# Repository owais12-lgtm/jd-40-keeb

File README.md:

# jd-40-keeb

# about

This is a keyboard based on the JD40 layout which has smaller keys and generally small form factor. it has a oled screen, encoder and a number pad

# Images

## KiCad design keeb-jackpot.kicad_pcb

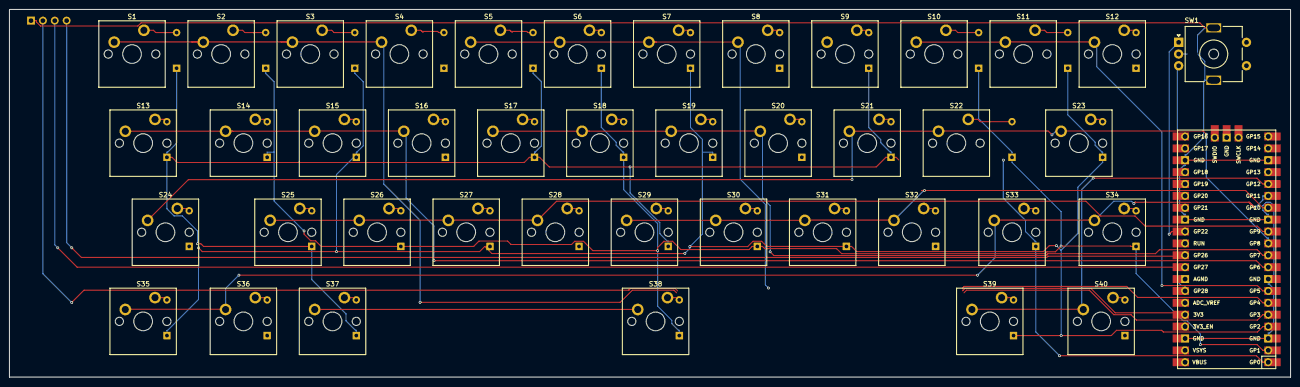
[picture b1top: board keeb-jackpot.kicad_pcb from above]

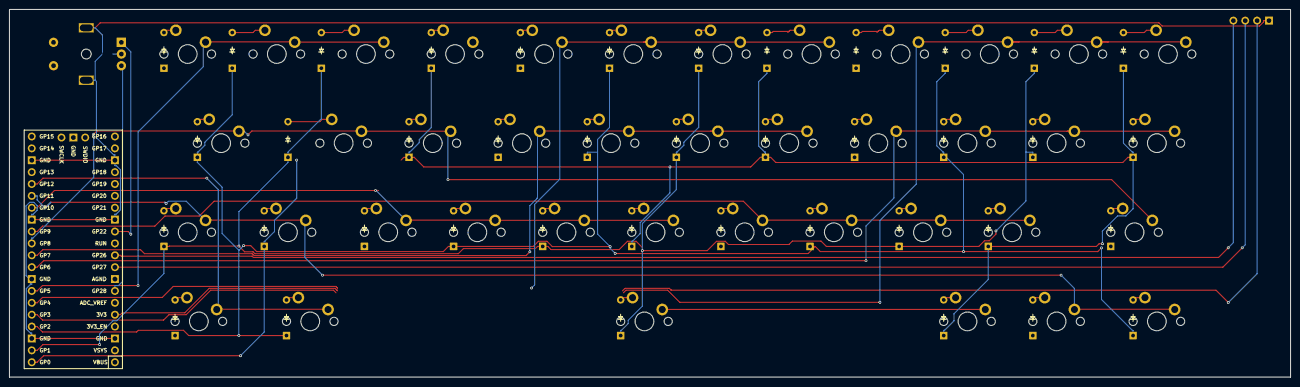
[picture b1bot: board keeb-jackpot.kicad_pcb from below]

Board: 2 copper layers, 273.8 x 78.6 mm, 83 parts (40 on the bottom side), 59 nets.

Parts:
D1, D2, D3, D4, D5, D6, D7, D8, D9, D10, D11, D12, D13, D14, D15, D16, D17, D18, D19, D20, D21, D22, D23, D24, D25, D26, D27, D28, D29, D30, D31, D32, D33, D34, D35, D36, D37, D38, D39, D40: Diode_DO-35
J1: OLED_128x32
S1, S2, S3, S4, S5, S6, S7, S8, S9, S10, S11, S12, S13, S14, S15, S16, S17, S18, S19, S20, S21, S22, S23, S24, S25, S26, S27, S28, S29, S30, S31, S32, S33, S34, S35, S36, S37, S38, S39, S40: MX_PCB_1.00u
SW1: RotaryEncoder_Switch_MP; RotaryEncoder_Alps_EC11E-Switch_Vertical_H20mm_MountingHoles
U1: Raspberry_Pi_Pico

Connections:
COL0: S1.1, S2.1, S3.1, S4.1, U1.5 (GPIO3)
COL1: S5.1, S6.1, S7.1, S8.1, U1.6 (GPIO4)
COL2: S9.1, S10.1, S11.1, S12.1, U1.7 (GPIO5)
COL3: S13.1, S14.1, S15.1, S16.1, U1.9 (GPIO6)
COL4: S17.1, S18.1, S19.1, S20.1, U1.10 (GPIO7)
COL5: S21.1, S22.1, S23.1, S24.1, U1.11 (GPIO8)
COL6: S25.1, S26.1, S27.1, S28.1, U1.12 (GPIO9)
COL7: S29.1, S30.1, S31.1, S32.1, U1.14 (GPIO10)
COL8: S33.1, S34.1, S35.1, S36.1, U1.15 (GPIO11)
COL9: S37.1, S38.1, S39.1, S40.1, U1.16 (GPIO12)
ENC_A: SW1.A, U1.29 (GPIO22)
ENC_B: SW1.B, U1.34 (GPIO28_ADC2)
GND: J1.1 (GND), SW1.C, SW1.MP, U1.3 (GND), U1.8 (GND), U1.13 (GND), U1.18 (GND), U1.23 (GND), U1.28 (GND), U1.38 (GND)
unnamed: D1.2 (A), S1.2
unnamed: D2.2 (A), S2.2
unnamed: D3.2 (A), S3.2
unnamed: D4.2 (A), S4.2
unnamed: D5.2 (A), S5.2
unnamed: D6.2 (A), S6.2
unnamed: D7.2 (A), S7.2
unnamed: D8.2 (A), S8.2
unnamed: D9.2 (A), S9.2
unnamed: D10.2 (A), S10.2
unnamed: D11.2 (A), S11.2
unnamed: D12.2 (A), S12.2
unnamed: D13.2 (A), S13.2
unnamed: D14.2 (A), S14.2
unnamed: D15.2 (A), S15.2
unnamed: D16.2 (A), S16.2
unnamed: D17.2 (A), S17.2
unnamed: D18.2 (A), S18.2
unnamed: D19.2 (A), S19.2
unnamed: D20.2 (A), S20.2
unnamed: D21.2 (A), S21.2
unnamed: D22.2 (A), S22.2
unnamed: D23.2 (A), S23.2
unnamed: D24.2 (A), S24.2
unnamed: D25.2 (A), S25.2
unnamed: D26.2 (A), S26.2
unnamed: D27.2 (A), S27.2
unnamed: D28.2 (A), S28.2
unnamed: D29.2 (A), S29.2
unnamed: D30.2 (A), S30.2
unnamed: D31.2 (A), S31.2
unnamed: D32.2 (A), S32.2
unnamed: D33.2 (A), S33.2
unnamed: D34.2 (A), S34.2
unnamed: D35.2 (A), S35.2
unnamed: D36.2 (A), S36.2
unnamed: D37.2 (A), S37.2
unnamed: D38.2 (A), S38.2
unnamed: D39.2 (A), S39.2
unnamed: D40.2 (A), S40.2
ROW0: D1.1 (K), D5.1 (K), D9.1 (K), D13.1 (K), D17.1 (K), D21.1 (K), D25.1 (K), D29.1 (K), D33.1 (K), D37.1 (K), U1.1 (GPIO0)
ROW1: D2.1 (K), D6.1 (K), D10.1 (K), D14.1 (K), D18.1 (K), D22.1 (K), D26.1 (K), D30.1 (K), D34.1 (K), D38.1 (K), U1.2 (GPIO1)
ROW2: D3.1 (K), D7.1 (K), D11.1 (K), D15.1 (K), D19.1 (K), D23.1 (K), D27.1 (K), D31.1 (K), D35.1 (K), D39.1 (K), U1.4 (GPIO2)
SCL: J1.3 (SCL), U1.32 (GPIO27_ADC1)
SDA: J1.4 (SDA), U1.31 (GPIO26_ADC0)
VCC: J1.2 (VCC), U1.36 (3V3)
